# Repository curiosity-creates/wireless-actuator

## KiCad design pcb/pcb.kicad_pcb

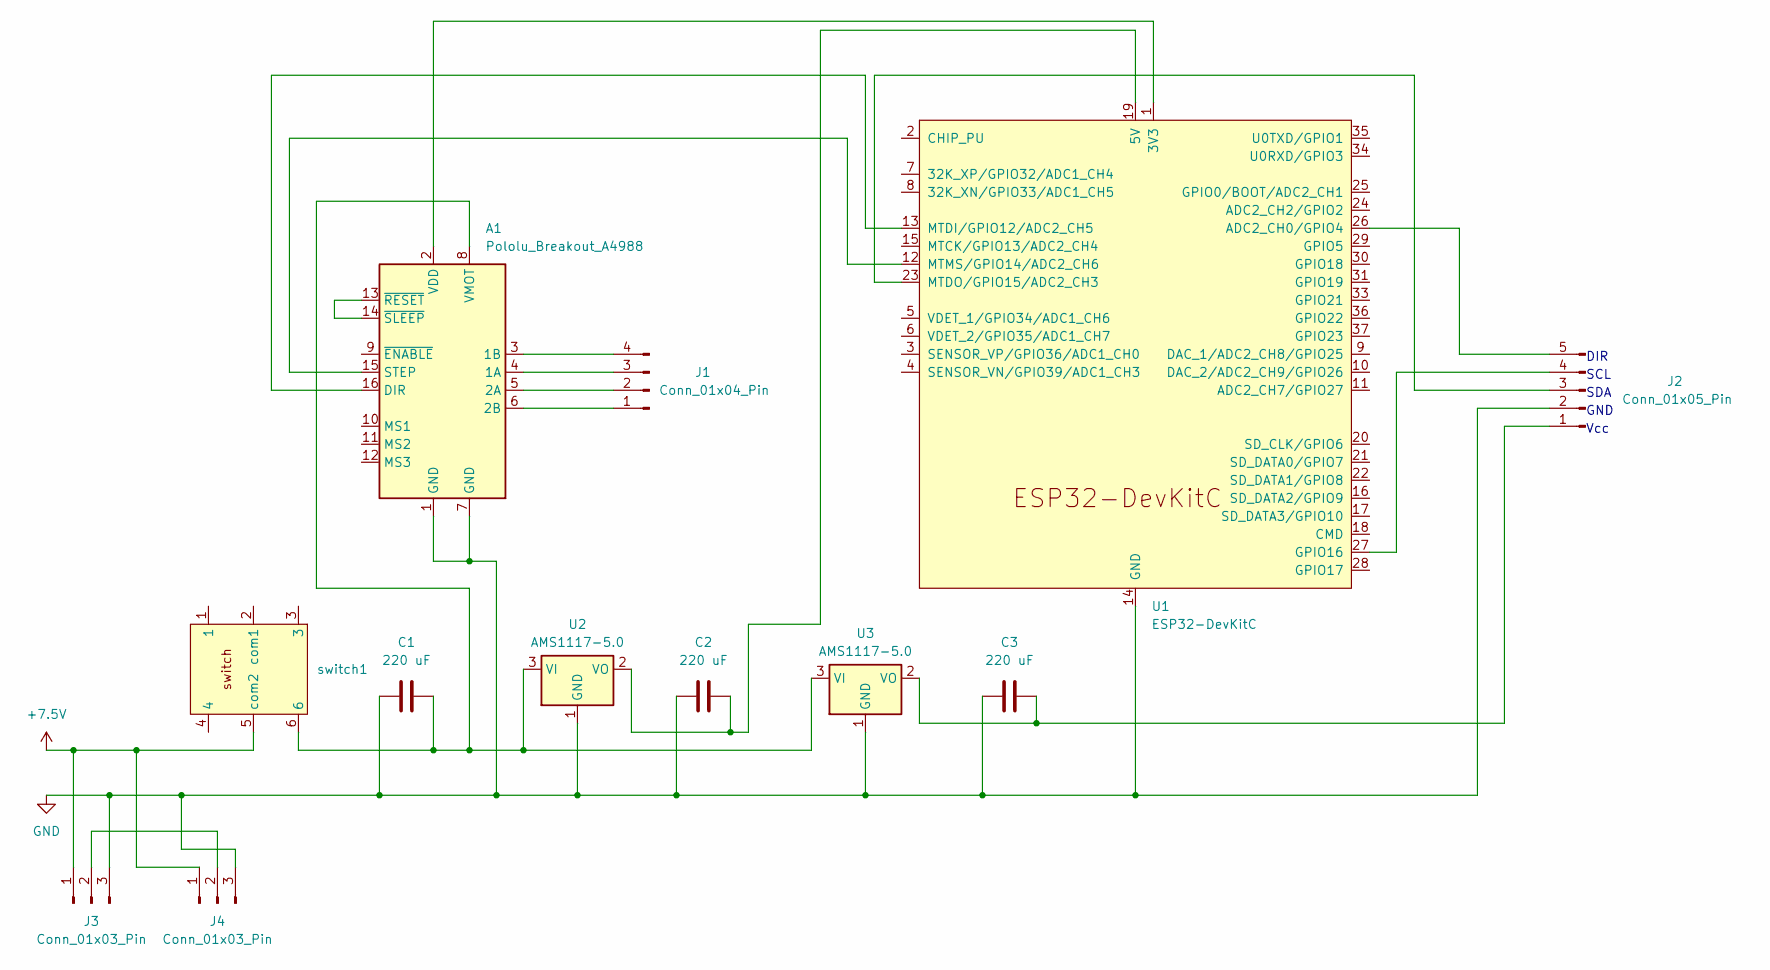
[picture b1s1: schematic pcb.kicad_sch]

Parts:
A1: Pololu_Breakout_A4988; Pololu_Breakout-16_15.2x20.3mm
C1, C2, C3: 220 uF; CP_Radial_D5.0mm_P2.00mm
J1: Conn_01x04_Pin; JST_XH_B4B-XH-AM_1x04_P2.50mm_Vertical
J2: Conn_01x05_Pin; JST_XH_B5B-XH-AM_1x05_P2.50mm_Vertical
J3, J4: Conn_01x03_Pin; JST_XH_B3B-XH-AM_1x03_P2.50mm_Vertical
U1: ESP32-DevKitC
U2, U3: AMS1117-5.0; SOT-223-3_TabPin2
switch1: micro_switch_6

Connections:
+7.5V: J3.1, J4.1, switch1.5 (com2)
GND: A1.1 (GND), A1.7 (GND), C1.2, C2.2, C3.2, J2.2, J3.3, J4.3, U1.14 (GND), U1.32 (GND), U1.38 (GND), U2.1 (GND), U3.1 (GND)
unnamed: A1.4 (1A), J1.3
unnamed: A1.3 (1B), J1.4
unnamed: A1.5 (2A), J1.2
unnamed: A1.6 (2B), J1.1
unnamed: A1.16 (DIR), U1.13 (MTDI/GPIO12/ADC2_CH5)
unnamed: A1.15 (STEP), U1.12 (MTMS/GPIO14/ADC2_CH6)
unnamed: A1.2 (VDD), U1.1 (3V3)
unnamed: A1.8 (VMOT), C1.1, U2.3 (VI), U3.3 (VI), switch1.6
unnamed: A1.13 (~RESET), A1.14 (~SLEEP)
unnamed: C3.1, J2.1, U3.2 (VO)
unnamed: J2.3, U1.23 (MTDO/GPIO15/ADC2_CH3)
unnamed: J2.4, U1.27 (GPIO16)
unnamed: J2.5, U1.26 (ADC2_CH0/GPIO4)
unnamed: J3.2, J4.2
unnamed: C2.1, U1.19 (5V), U2.2 (VO)

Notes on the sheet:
SCL
GND
DIR
SDA
Vcc

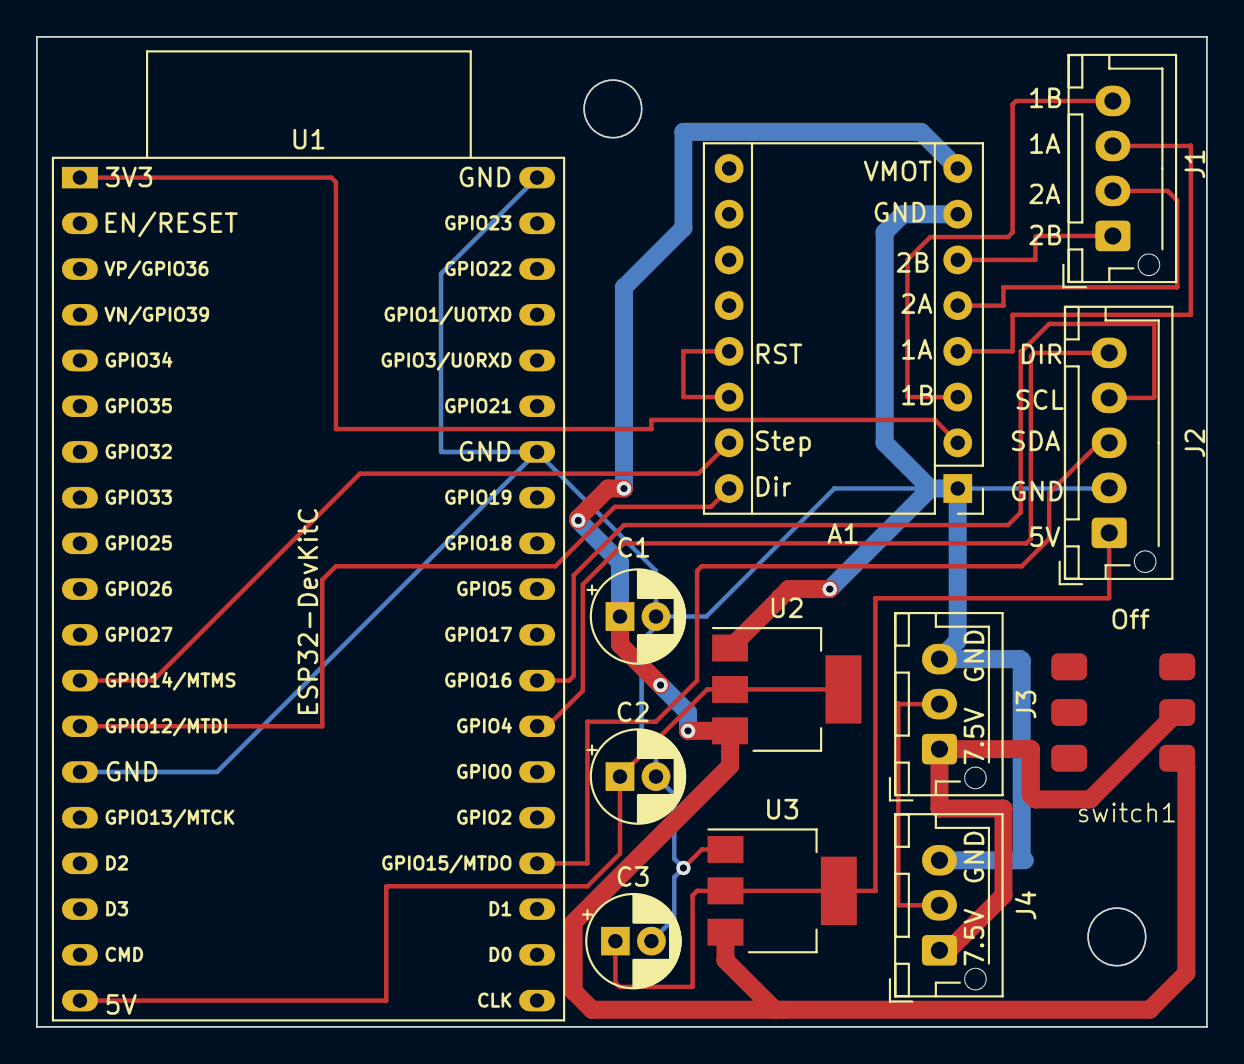
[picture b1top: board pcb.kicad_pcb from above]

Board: 2 copper layers, 65.0 x 55.0 mm, 12 parts (0 on the bottom side), 17 nets.

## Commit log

2024-03-01 Create pcb
